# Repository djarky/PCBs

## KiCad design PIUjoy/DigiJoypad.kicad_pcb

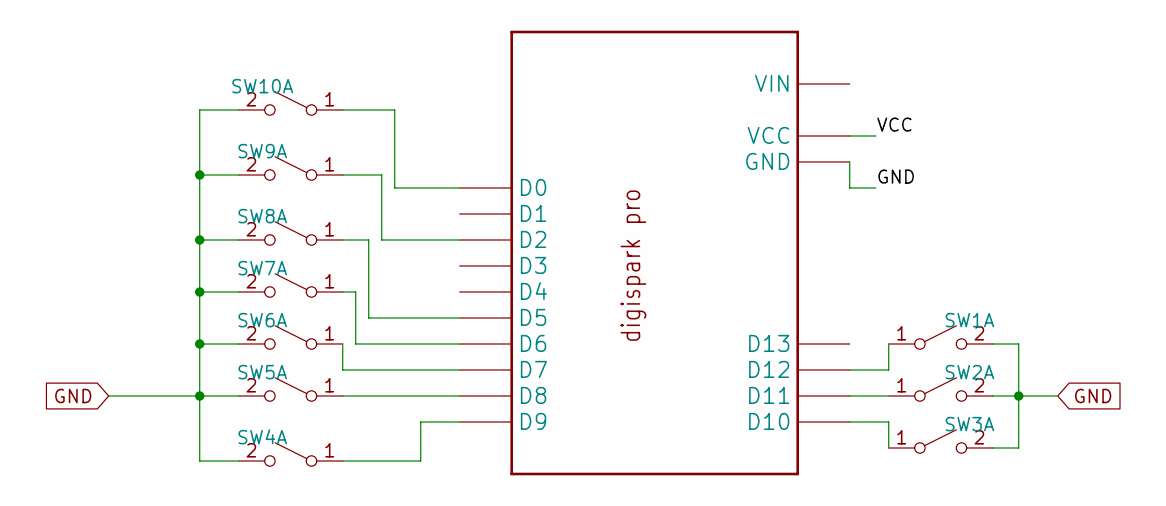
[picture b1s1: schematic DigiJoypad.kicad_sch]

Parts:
SW1, SW2, SW3, SW4, SW5, SW6, SW7, SW8, SW9, SW10: SW_MEC_5G; SW_SPST_Omron_B3F-40xx
U$1: DIGI-PRO

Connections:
/VCC: U$1.VCC, U$1.VCC1 (VCC)
GND: SW1.2 (B), SW2.2 (B), SW3.2 (B), SW4.2 (B), SW5.2 (B), SW6.2 (B), SW7.2 (B), SW8.2 (B), SW9.2 (B), SW10.2 (B), U$1.GND
unnamed: SW1.1 (A), U$1.D12
unnamed: SW2.1 (A), U$1.D11
unnamed: SW3.1 (A), U$1.D10
unnamed: SW4.1 (A), U$1.D9
unnamed: SW5.1 (A), U$1.D8
unnamed: SW6.1 (A), U$1.D7
unnamed: SW7.1 (A), U$1.D6
unnamed: SW8.1 (A), U$1.D5
unnamed: SW9.1 (A), U$1.D2
unnamed: SW10.1 (A), U$1.D0

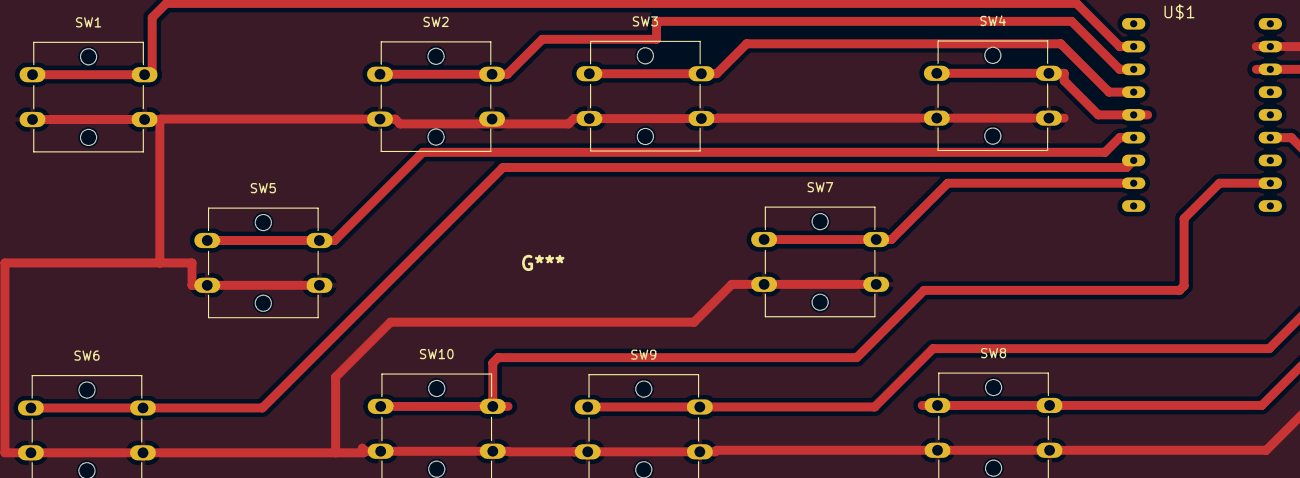
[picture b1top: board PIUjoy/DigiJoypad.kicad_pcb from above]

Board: 2 copper layers, 11 parts (0 on the bottom side), 12 nets.

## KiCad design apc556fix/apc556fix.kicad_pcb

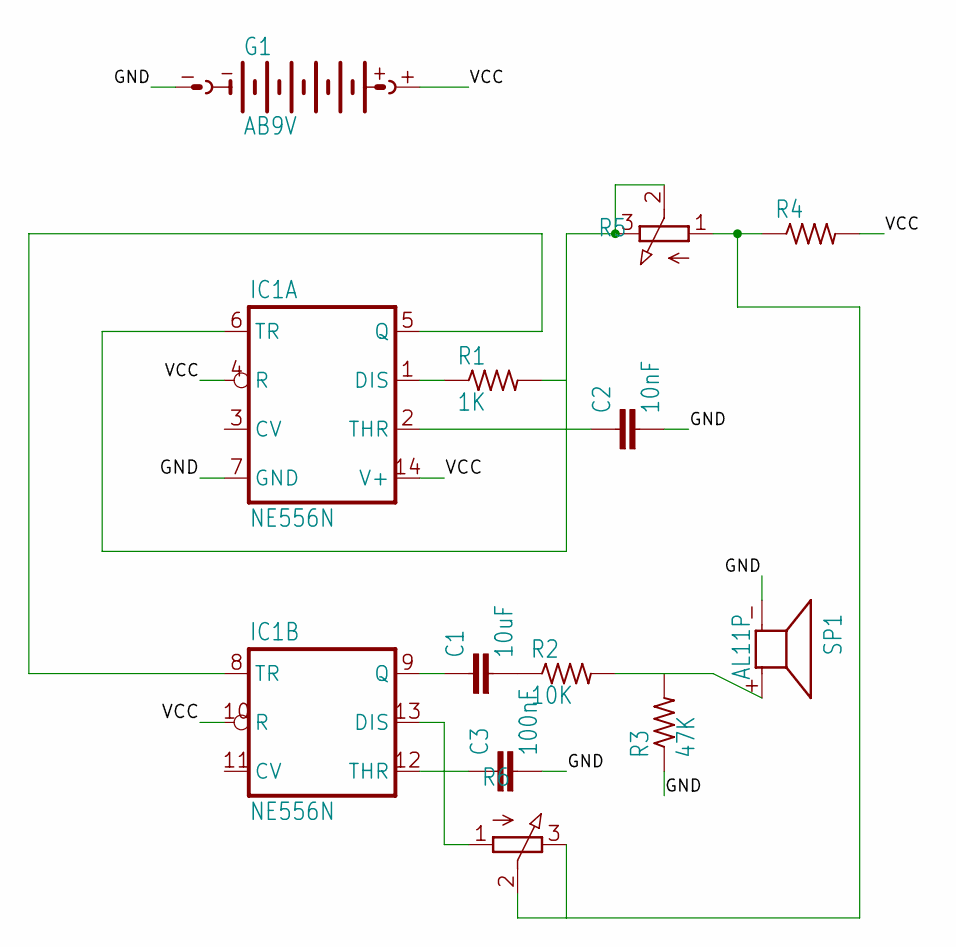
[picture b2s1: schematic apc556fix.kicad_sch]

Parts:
C1: 10uF; C025-030X050
C2: 10nF; C025-030X050
C3: 100nF; C025-030X050
G1: AB9V
IC1: NE556N; DIL14
R1: 1K; 0204_5
R2: 10K; 0204_7
R3: 47K; 0204_7
R4: 0204_7
R5, R6: 3RP_1610N
SP1: AL11P

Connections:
/GND: C2.2, C3.2, G1.-, IC1.7 (GND), R3.1, SP1.- (1)
/VCC: G1.+, IC1.4 (R), IC1.10 (R), IC1.14 (V+), R4.2
unnamed: C1.2, R2.1
unnamed: IC1.1 (DIS), R1.1
unnamed: IC1.5 (Q), IC1.8 (TR)
unnamed: C2.1, IC1.2 (THR), IC1.6 (TR), R1.2, R5.2 (S), R5.3 (E)
unnamed: C3.1, IC1.12 (THR), IC1.13 (DIS), R6.1 (A)
unnamed: C1.1, IC1.9 (Q)
unnamed: R4.1, R5.1 (A), R6.2 (S), R6.3 (E)
unnamed: R2.2, R3.2, SP1.+ (2)

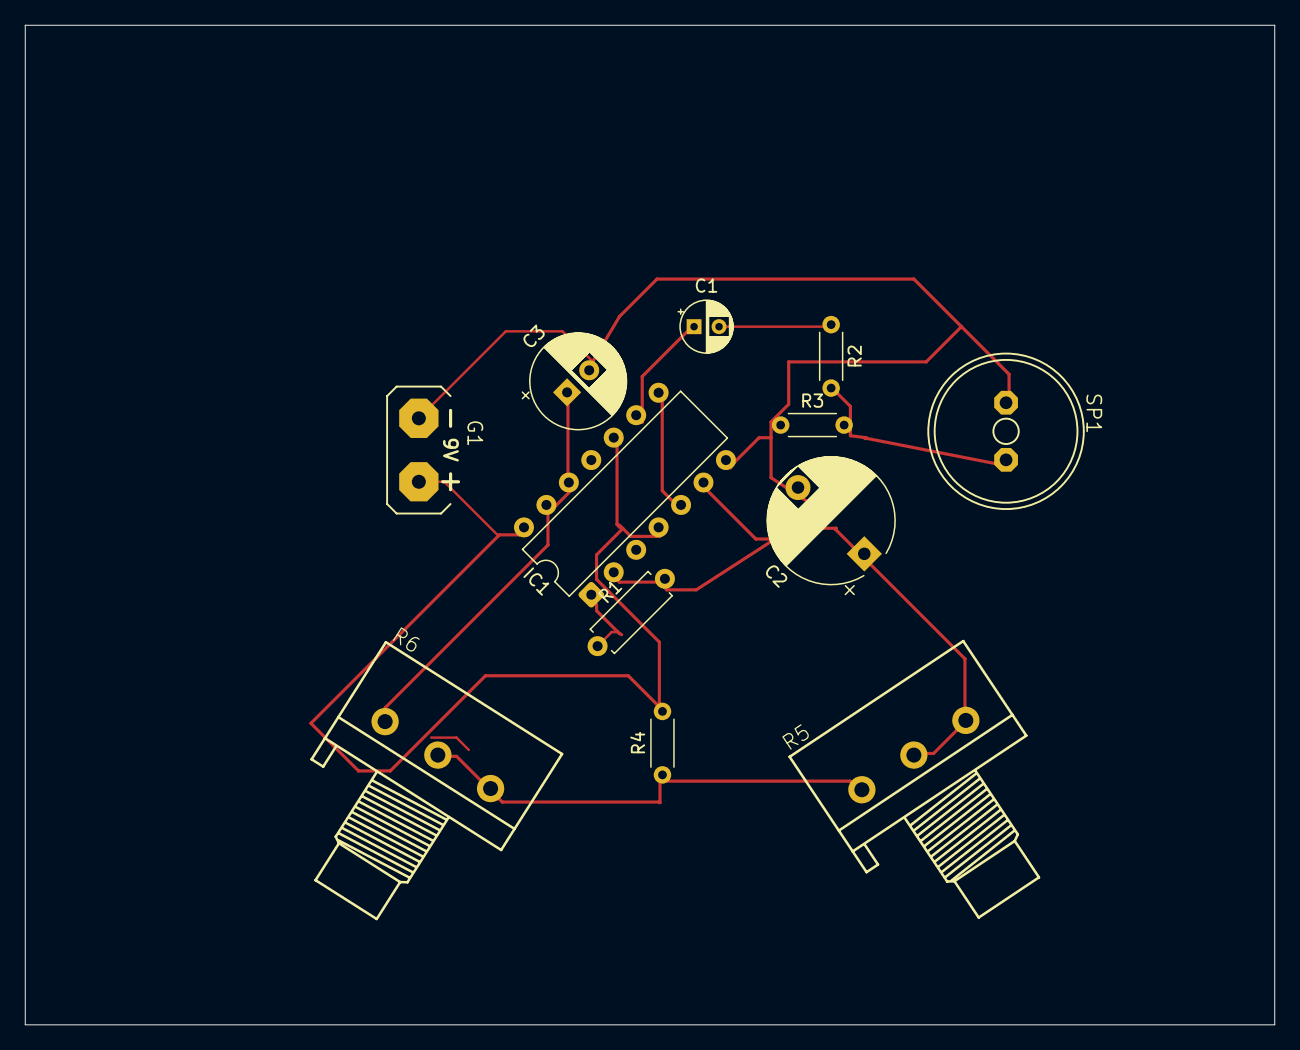
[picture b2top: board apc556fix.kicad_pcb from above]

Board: 2 copper layers, 100.0 x 80.0 mm, 12 parts (0 on the bottom side), 10 nets.

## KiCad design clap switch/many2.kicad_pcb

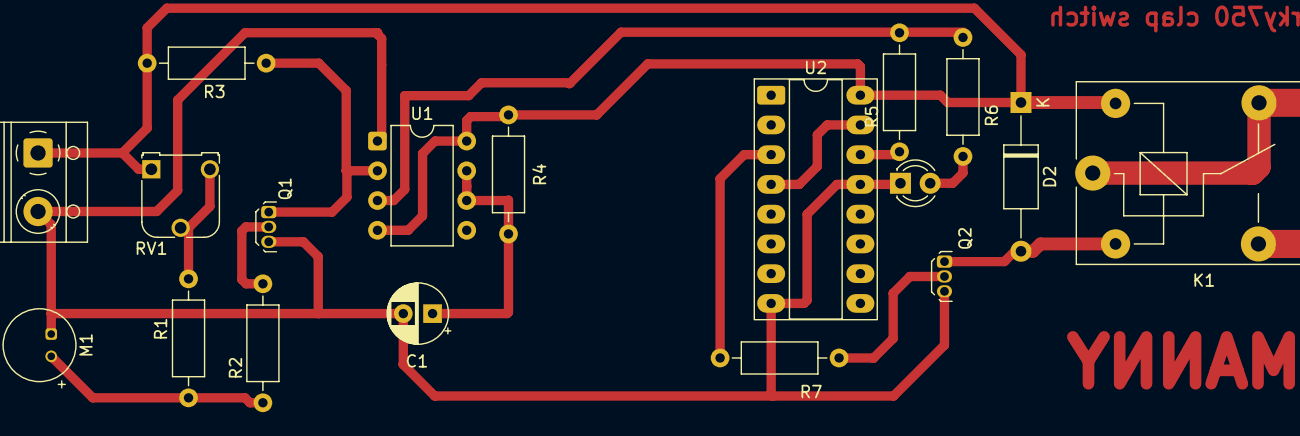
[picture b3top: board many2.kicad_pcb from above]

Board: 2 copper layers, 18 parts (0 on the bottom side), 15 nets.

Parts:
BT1: Battery; TerminalBlock_RND_205-00012_1x02_P5.00mm_Horizontal
C1: C_Polarized; CP_Radial_D5.0mm_P2.50mm
D1: LED; LED_D3.0mm_Clear
D2: D; D_A-405_P12.70mm_Horizontal
K1: Relay_DPDT; Relay_SPDT_SANYOU_SRD_Series_Form_C
M1: Microphone; POM-2244P-C3310-2-R
Q1, Q2: NPN; TO-92Flat
R1: 10K; R_Axial_DIN0207_L6.3mm_D2.5mm_P10.16mm_Horizontal
R2, R4, R5, R7: 1K; R_Axial_DIN0207_L6.3mm_D2.5mm_P10.16mm_Horizontal
R3: 100K; R_Axial_DIN0207_L6.3mm_D2.5mm_P10.16mm_Horizontal
R6: 330; R_Axial_DIN0207_L6.3mm_D2.5mm_P10.16mm_Horizontal
RV1: 100K; Potentiometer_Runtron_RM-065_Vertical
U1: NE555P; DIP-8_W7.62mm
U2: 4017; DIP-16_W7.62mm_Socket_LongPads

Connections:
GND: BT1.2 (-), C1.2, D1.1 (K), M1.1 (-), Q1.3 (E), Q2.3 (E), U1.1 (GND), U2.8 (VSS), U2.13 (CKEN)
K1: K1.1, K1.4
unnamed: D1.2 (A), R6.2
unnamed: D2.2 (A), K1.2, Q2.1 (C)
unnamed: M1.2 (+), R1.2, R2.2
unnamed: Q1.2 (B), R2.1
unnamed: Q1.1 (C), R3.2, U1.2 (TR)
unnamed: Q2.2 (B), R7.2
unnamed: R1.1, RV1.2, RV1.3
unnamed: C1.1, R4.2, U1.6 (THR), U1.7 (DIS)
unnamed: R5.2, R6.1, U1.3 (Q)
unnamed: R5.1, U2.14 (CLK)
unnamed: R7.1, U2.3 (Q0)
unnamed: U2.4 (Q2), U2.15 (Reset)
VCC: BT1.1 (+), D2.1 (K), K1.5, R3.1, R4.1, RV1.1, U1.4 (R), U1.8 (VCC), U2.16 (VDD)

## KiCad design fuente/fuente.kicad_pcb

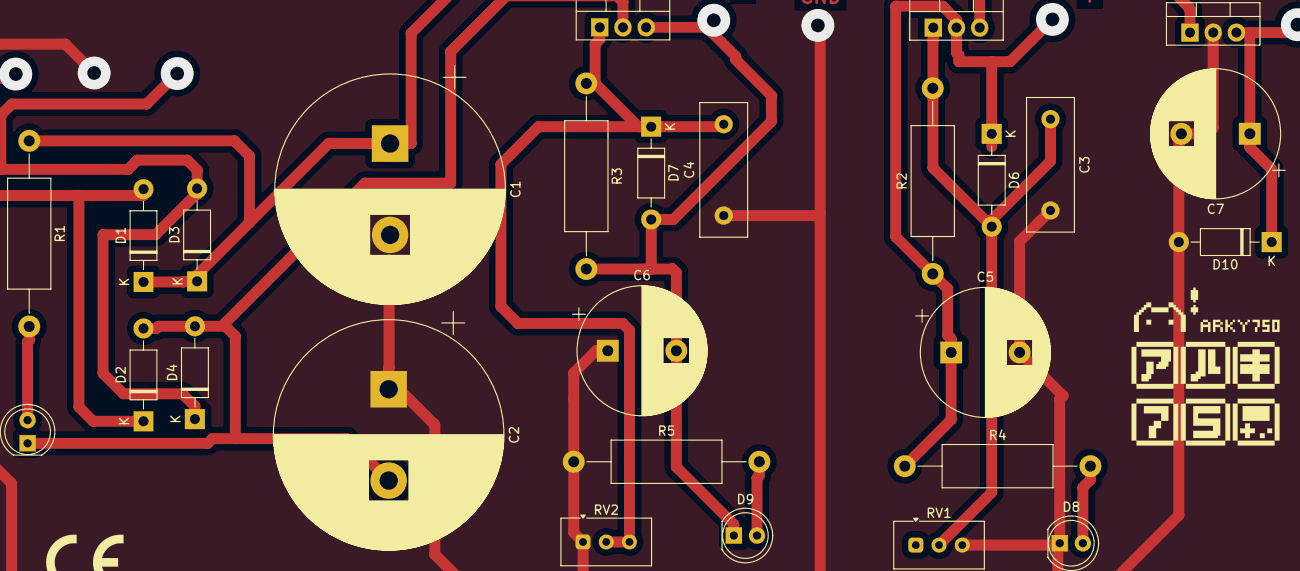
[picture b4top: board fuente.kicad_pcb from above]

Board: 2 copper layers, 27 parts (0 on the bottom side), 13 nets.

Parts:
C1, C2: 2200u; CP_Radial_D25.0mm_P10.00mm_SnapIn
C3: 100n; C_Disc_D14.5mm_W5.0mm_P10.00mm
C4: C; C_Disc_D14.5mm_W5.0mm_P10.00mm
C5, C6, C7: 1uF; CP_Radial_D14.0mm_P7.50mm
D1, D2, D3, D4, D6, D7, D10: 1N4007; D_DO-41_SOD81_P10.16mm_Horizontal
D5, D8, D9: LED; LED_D5.0mm
R1: 4.7k; R_Axial_DIN0414_L11.9mm_D4.5mm_P20.32mm_Horizontal
R2, R3: 220; R_Axial_DIN0414_L11.9mm_D4.5mm_P20.32mm_Horizontal
R4, R5: 1K; R_Axial_DIN0414_L11.9mm_D4.5mm_P20.32mm_Horizontal
RV1, RV2: 5K; Potentiometer_Vishay_T93YA_Vertical
U1: LM317_TO-220; TO-220-3_Vertical
U2: LM337_TO220; TO-220-3_Vertical
U3: LM7805_TO220; TO-220-3_Vertical

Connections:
5V: C7.1, D10.1 (K), U3.3 (VO)
+: C5.1, D6.1 (K), R2.1, R4.1, U1.2 (VO)
-: C6.2, D7.2 (A), D9.1 (K), R3.2, U2.3 (VO)
GND: C1.2, C2.1, C3.2, C4.1, C5.2, C6.1, C7.2, D8.1 (K), D10.2 (A), R5.1, RV1.3, RV2.1, U3.2 (GND)
unnamed: C1.1, D1.1 (K), D3.1 (K), R1.1, U1.3 (VI), U3.1 (VI)
unnamed: C2.2, D2.2 (A), D4.2 (A), D5.1 (K), U2.2 (VI)
unnamed: D5.2 (A), R1.2
unnamed: C3.1, D6.2 (A), R2.2, RV1.1, RV1.2, U1.1 (ADJ)
unnamed: C4.2, D7.1 (K), R3.1, RV2.2, RV2.3, U2.1 (ADJ)
unnamed: D8.2 (A), R4.2
unnamed: D9.2 (A), R5.2
TR1: D1.2 (A), D2.1 (K)
TR3: D3.2 (A), D4.1 (K)

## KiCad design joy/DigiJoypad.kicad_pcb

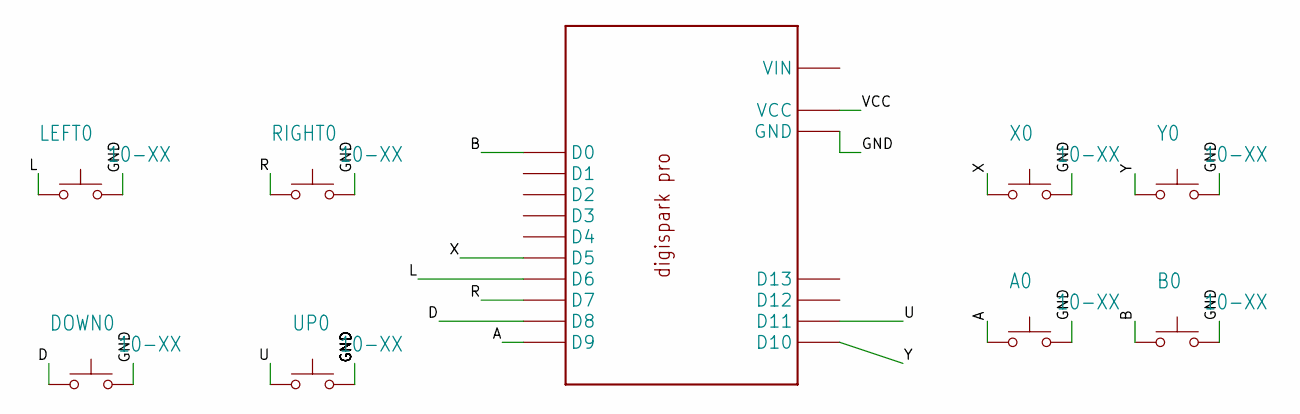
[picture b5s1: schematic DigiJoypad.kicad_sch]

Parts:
A0: 10-XX; B3F-10XX
B0: 10-XX; B3F-10XX
DOWN0: 10-XX; B3F-10XX
LEFT0: 10-XX; B3F-10XX
RIGHT0: 10-XX; B3F-10XX
U$1: DIGI-PRO
UP0: 10-XX; B3F-10XX
X0: 10-XX; B3F-10XX
Y0: 10-XX; B3F-10XX

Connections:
/A: A0.1, U$1.D9
/B: B0.1, U$1.D0
/D: DOWN0.1, U$1.D8
/GND: A0.2, B0.2, DOWN0.2, LEFT0.2, RIGHT0.2, U$1.GND, UP0.2, X0.2, Y0.2
/L: LEFT0.1, U$1.D6
/R: RIGHT0.1, U$1.D7
/U: U$1.D11, UP0.1
/VCC: U$1.VCC, U$1.VCC1 (VCC)
/X: U$1.D5, X0.1
/Y: U$1.D10, Y0.1

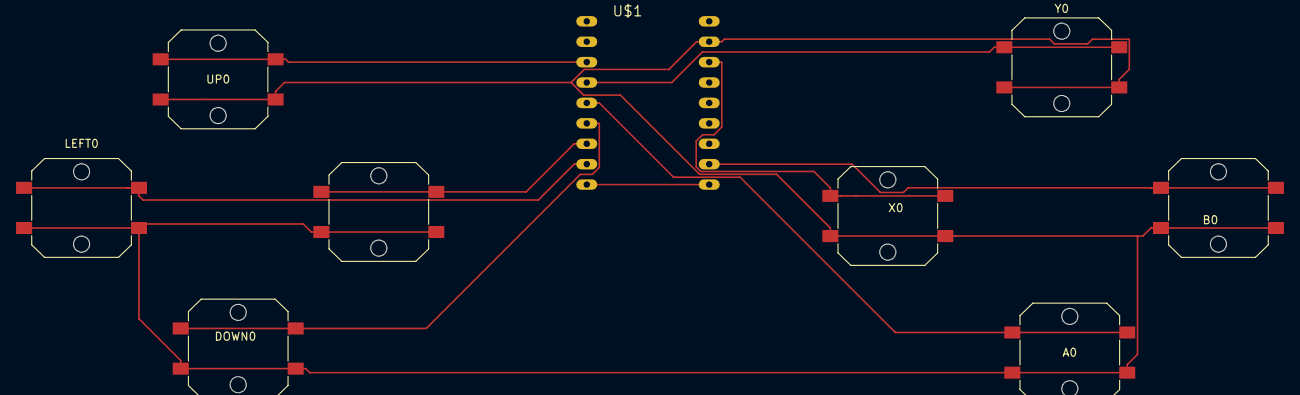
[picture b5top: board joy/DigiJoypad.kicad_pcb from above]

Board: 2 copper layers, 9 parts (0 on the bottom side), 10 nets.

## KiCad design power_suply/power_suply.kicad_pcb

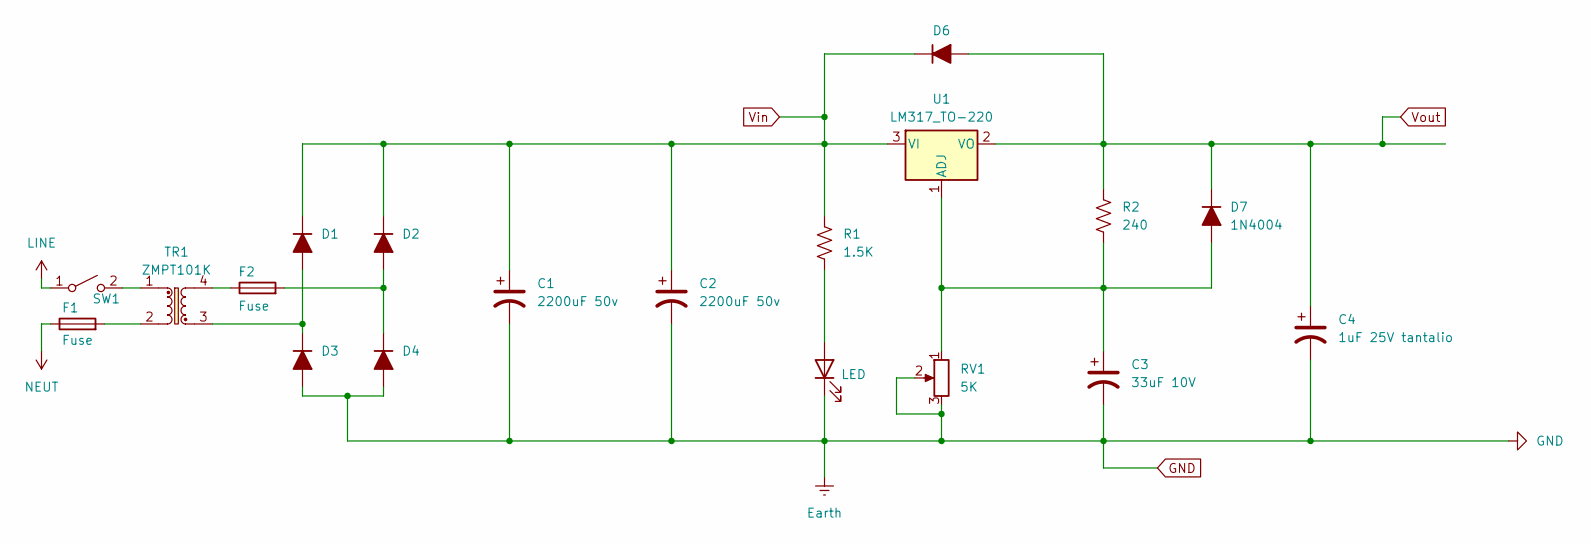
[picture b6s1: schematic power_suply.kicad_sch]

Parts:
C1, C2: 2200uF 50v; CP_Radial_D24.0mm_P10.00mm_SnapIn
C3: 33uF 10V; CP_Radial_D8.0mm_P5.00mm
C4: 1uF 25V tantalio; CP_Radial_Tantal_D9.0mm_P5.00mm
D1, D2, D3, D4: D_Filled; D_DO-201AD_P15.24mm_Horizontal
D5: LED; LED_D8.0mm
D6: D_Filled; D_A-405_P10.16mm_Horizontal
D7: 1N4004; D_A-405_P10.16mm_Horizontal
F1, F2: Fuse; Fuseholder_Clip-5x20mm_Littelfuse_111_Lateral_P18.80x5.00mm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
R1: 1.5K; R_Axial_DIN0614_L14.3mm_D5.7mm_P20.32mm_Horizontal
R2: 240; R_Axial_DIN0614_L14.3mm_D5.7mm_P20.32mm_Horizontal
RV1: 5K; Potentiometer_Vishay_T93YA_Vertical
SW1: SW_SPST; SW_DIP_SPSTx01_Slide_9.78x4.72mm_W7.62mm_P2.54mm
TR1: ZMPT101K; Transformer_Zeming_ZMPT101K
U1: LM317_TO-220; TO-220-3_Vertical

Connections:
GND: C1.2, C2.2, C3.2, C4.2, D3.2 (A), D4.2 (A), D5.1 (K), RV1.2, RV1.3
LINE: SW1.1 (A)
NEUT: F1.1
unnamed: D1.2 (A), D3.1 (K), TR1.3
unnamed: D2.2 (A), D4.1 (K), F2.2
unnamed: D5.2 (A), R1.2
unnamed: C3.1, D7.2 (A), R2.2, RV1.1, U1.1 (ADJ)
unnamed: F1.2, TR1.2
unnamed: F2.1, TR1.4
unnamed: SW1.2 (B), TR1.1
Vin: C1.1, C2.1, D1.1 (K), D2.1 (K), D6.1 (K), R1.1, U1.3 (VI)
Vout: C4.1, D6.2 (A), D7.1 (K), R2.1, U1.2 (VO)

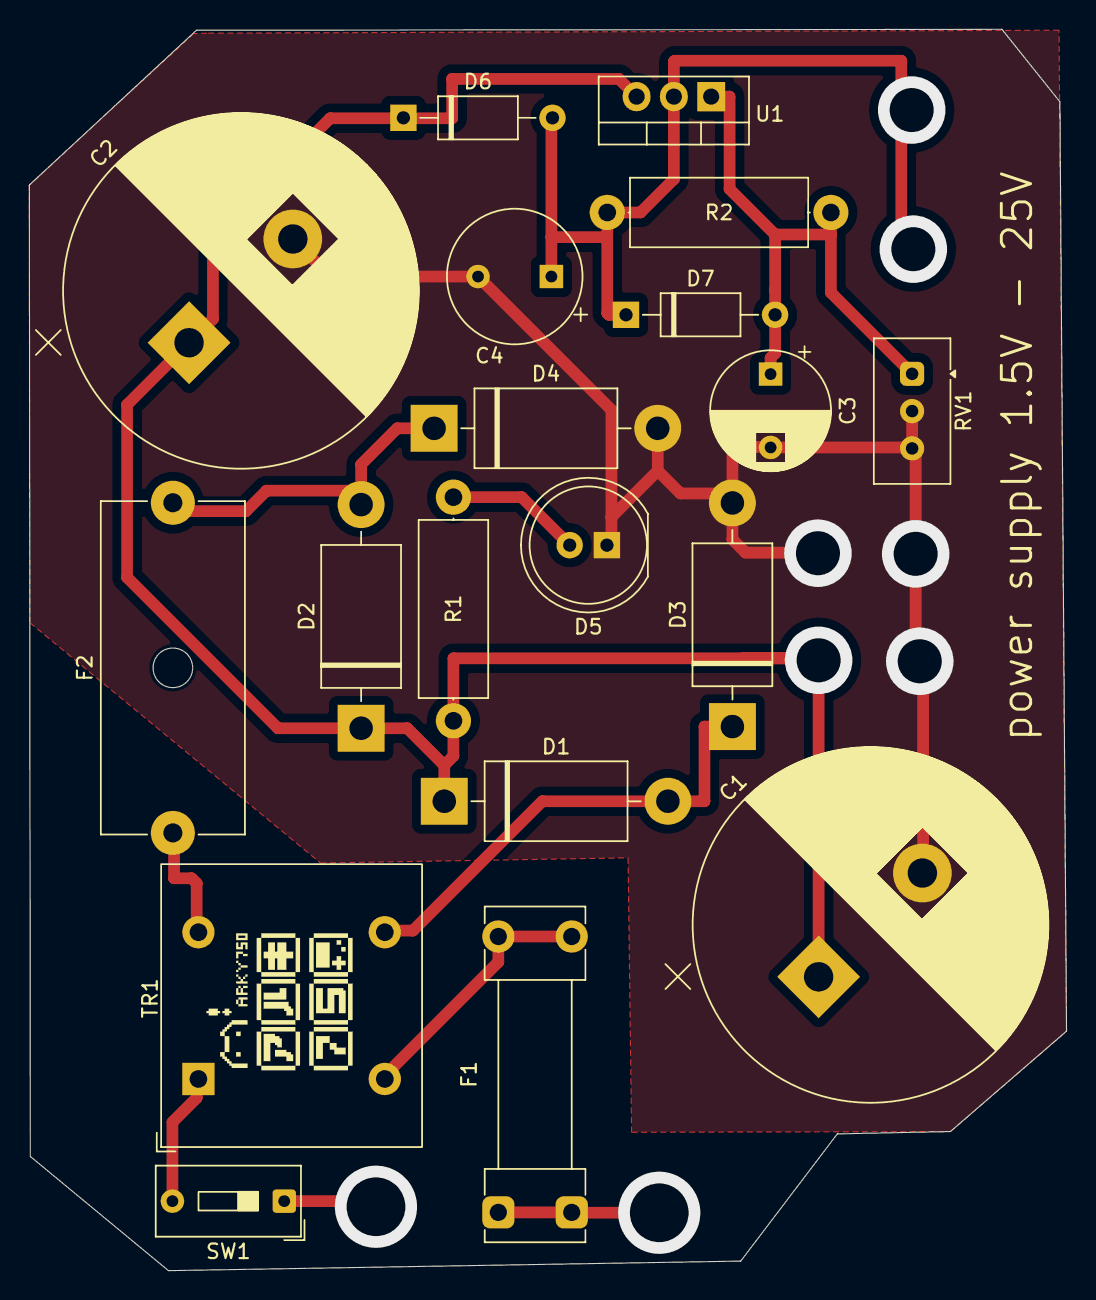
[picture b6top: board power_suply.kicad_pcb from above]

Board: 2 copper layers, 70.7 x 84.6 mm, 19 parts (0 on the bottom side), 10 nets.
